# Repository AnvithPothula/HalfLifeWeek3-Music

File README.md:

# HalfLifeWeek3-Music
Guide: https://github.com/KaiPereira/MIDI-Keypad/blob/master/README.md

I followed the guide to create the MIDI keypad. However, I made some changes. I added a second encoder, and since I decided to use both encoders clicking functionalities, I had to remove the low-profile switches and a slider to make room on the ESP32. The remaining slider is used for volume, the first encoder for changing octaves, and the second encoder for adding a modulation effect. This is the final result of how the PCB looks like:

**3D Model / Final PCB Render:**

**Schematic:**

**Board Layout & Routing:**

Combined Layout:

Front Copper Layer:

Back Copper Layer:

**What it is and how it works:**

This project is a MIDI keyboard built around the Waveshare ESP32-S3-Zero microcontroller. All of the components fit together on a single two-layer PCB:

* **Waveshare ESP32-S3-Zero:** Kind of like the brain of the board. It reads all touch, switch, encoder, and analog inputs and sends USB MIDI messages to a computer or DAW.
* **Capacitive Touch Keys:** There are 7 copper pads in the front layer of the PCB. The ESP32-S3's built-in capacitive touch pins detect when your finger touches a pad to trigger MIDI note-on and note-off events.
* **2 EC11 Rotary Encoders:** One encoder adds a modulation effect, while the second encoder shifts the keypad's active octave up and down.
* **Slide Potentiometer:** Connected to the ESP32-S3's ADC pins and changes the volume.
* **3 SK6812 MINI-E NeoPixels:** RGB LEDs on the back that shine through holes in the PCB. They light up in different colors to indicate button presses and also show the current octave.

**Why I made it:**

I made this project to get more experience with KiCad PCB design (specifically working with custom footprints like capacitive touch pads and reverse-mount LEDs). Just like in Week 1, I wanted to push past the basic guide by adding both hardware and software upgrades.

**How to assemble and flash the firmware:**

**1. How to flash the firmware**
You can flash this board using the Arduino IDE (or CircuitPython/KMK):

1. Install the Arduino IDE.
2. In the Boards Manager, install the ESP32 boards package by Espressif and select Waveshare ESP32-S3-Zero (or ESP32S3 Dev Module) as your board.
3. Under the Tools menu, set USB Mode to USB-OTG (TinyUSB) and USB CDC On Boot to Enabled so the board is recognized as a native USB MIDI device.
4. Install these libraries in the Library Manager:
   * Adafruit TinyUSB Library (or Control Surface / MIDI library)
   * Adafruit NeoPixel
   * ESP32Encoder
5. Open midi-keyboard-arduino/midi-keyboard-arduino.ino, plug the board into your computer via USB-C, and click Upload. If it doesn't upload automatically, hold the BOOT button on the ESP32-S3-Zero, tap RESET, and release BOOT to enter bootloader mode.

**2. How to assemble the board**
To assemble the keypad, you need a soldering iron, solder, flux, tweezers, and flush cutters. Solder the components from shortest/surface-mount to tallest/through-hole:

1. **SK6812 MINI-E NeoPixels:** These are on the back of the PCB so they shine through the front holes. Align the angled/notched corner of each LED with the ground/orientation mark on the silkscreen, put one pad down, check that it sits flat over the hole, and solder the remaining three pads.
2. **Waveshare ESP32-S3-Zero:** Place it on its footprint with the USB-C port facing outward toward the top edge of the board. Solder one corner pin first to check alignment, then solder the rest of the pins and check for solder bridges.
3. **EC11 Rotary Encoders:** Push the mounting legs and signal pins through the front of the PCB. Bend the two large side mounting tabs slightly if needed to hold them flush, then solder the 3 signal pins, 2 switch pins, and mounting tabs on the back.
4. **Slide Potentiometer:** Insert the slide potentiometer on the front of the board, make sure it sits completely straight and flat, and solder all pins on the back.
5. **Knobs:** Push the knobs onto the rotary encoders and slide potentiometers.

Before plugging in the USB-C cable, use a multimeter in continuity mode to make sure 3V3/5V and GND are not shorted. Once verified, plug it in, flash the firmware, and test the capacitive keys and encoders!

**BOM:**

| Item | Qty | Supplier | Cost/item | Total cost | Link |
| --- | ---: | --- | ---: | ---: | --- |
| ESP32-S3-Zero | 1 | AliExpress | $4.32 | $4.32 | [AliExpress](https://www.aliexpress.us/item/3256807949476561.html) |
| EC11 Rotary Encoder 20mm (5-pack) | 1 | AliExpress | $3.36 | $3.36 | [AliExpress](https://www.aliexpress.us/item/3256808530463909.html) |
| SK6812 MINI-E NeoPixels (20-pack) | 1 | AliExpress | $2.54 | $2.54 | [AliExpress](https://www.aliexpress.us/item/3256805007401420.html) |
| 45mm Slide Potentiometer B10K (5-pack) | 1 | AliExpress | $5.13 | $5.13 | [AliExpress](https://www.aliexpress.us/item/3256808872395865.html) |
| PCB | 1 | JLCPCB | $4.00 | $4.00 | [JLCPCB](https://jlcpcb.com/) |
| Shipping (AliExpress Choice) | — | AliExpress | — | $0.00 | — |
| Shipping (JLCPCB Global Standard Direct Line) | — | JLCPCB | — | $8.37 | — |
| Estimated sales tax (8.125% on AliExpress parts) | — | — | — | $1.25 | — |
| **Estimated total** |  |  |  | **$28.97** |  |

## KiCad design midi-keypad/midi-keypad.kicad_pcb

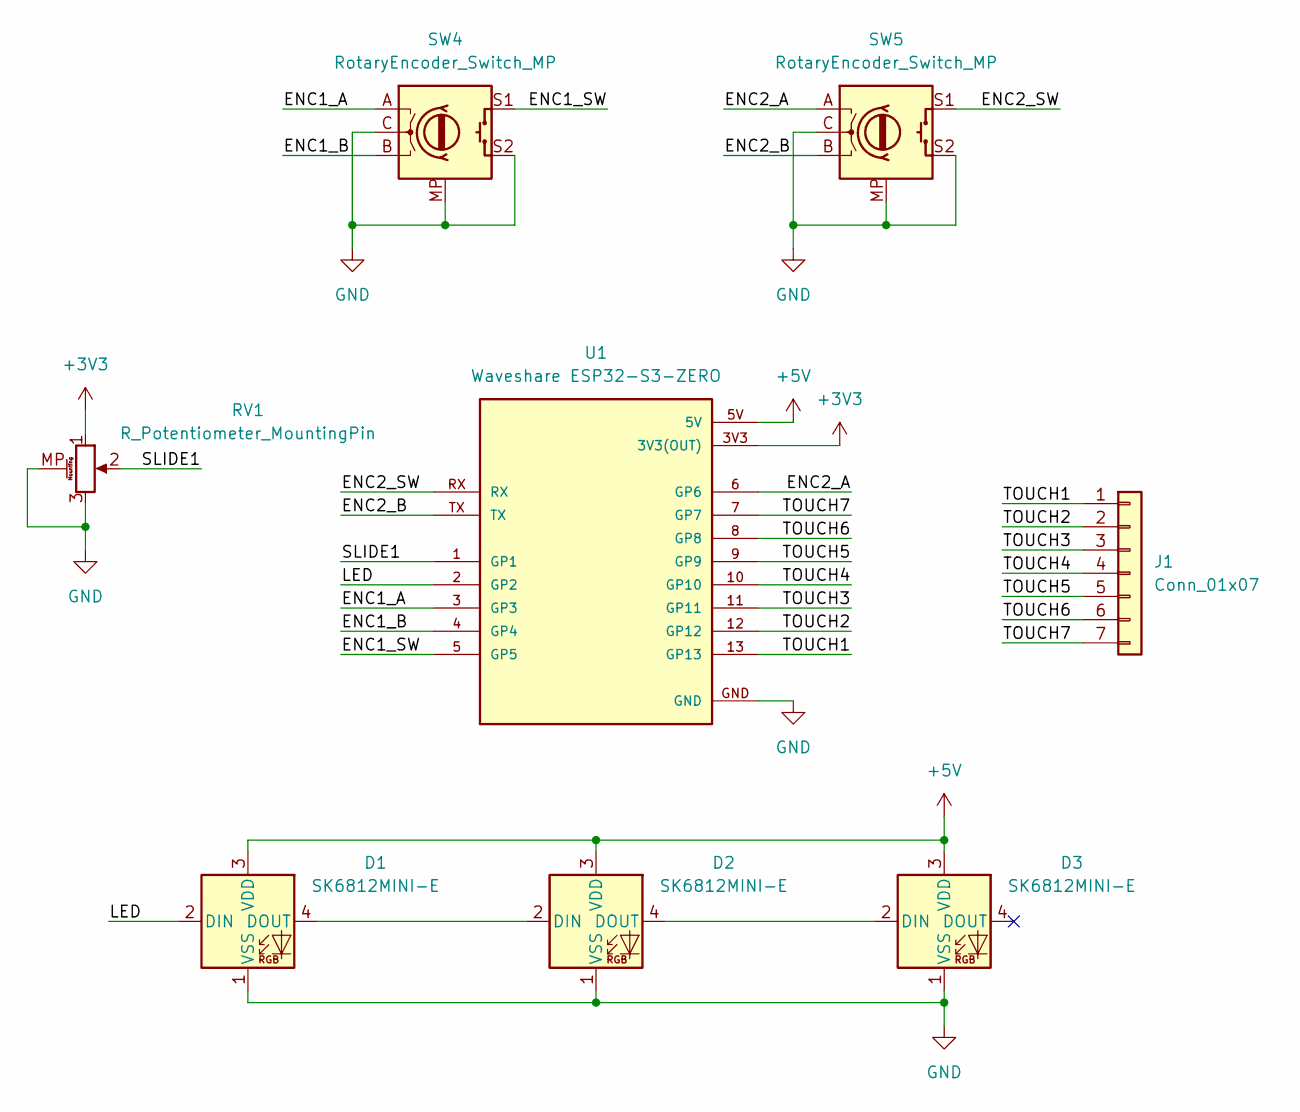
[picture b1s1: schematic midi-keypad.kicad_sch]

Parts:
D1, D2, D3: SK6812MINI-E; LED_SK6812MINI-E_3.2x2.8mm_P1.5mm_ReverseMount
J1: Conn_01x07; Capacitive Keys_7
RV1: R_Potentiometer_MountingPin; Potentiometer_Bourns_PTA1543_Single_Slide
SW4, SW5: RotaryEncoder_Switch_MP; RotaryEncoder_Alps_EC11E-Switch_Vertical_H20mm
U1: Waveshare ESP32-S3-ZERO; Waveshare ESP32-S3-Zero; PARTREV NA

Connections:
+3V3: RV1.1, U1.3V3 (3V3(OUT))
+5V: D1.3 (VDD), D2.3 (VDD), D3.3 (VDD), U1.5V
/ENC1_A: SW4.A, U1.3 (GP3)
/ENC1_B: SW4.B, U1.4 (GP4)
/ENC1_SW: SW4.S1, U1.5 (GP5)
/ENC2_A: SW5.A, U1.6 (GP6)
/ENC2_B: SW5.B, U1.TX
/ENC2_SW: SW5.S1, U1.RX
/LED: D1.2 (DIN), U1.2 (GP2)
/SLIDE1: RV1.2, U1.1 (GP1)
/TOUCH1: J1.1, U1.13 (GP13)
/TOUCH2: J1.2, U1.12 (GP12)
/TOUCH3: J1.3, U1.11 (GP11)
/TOUCH4: J1.4, U1.10 (GP10)
/TOUCH5: J1.5, U1.9 (GP9)
/TOUCH6: J1.6, U1.8 (GP8)
/TOUCH7: J1.7, U1.7 (GP7)
GND: D1.1 (VSS), D2.1 (VSS), D3.1 (VSS), RV1.3, RV1.MP (MountPin), SW4.C, SW4.MP, SW4.S2, SW5.C, SW5.MP, SW5.S2, U1.GND
unnamed: D1.4 (DOUT), D2.2 (DIN)
unnamed: D2.4 (DOUT), D3.2 (DIN)

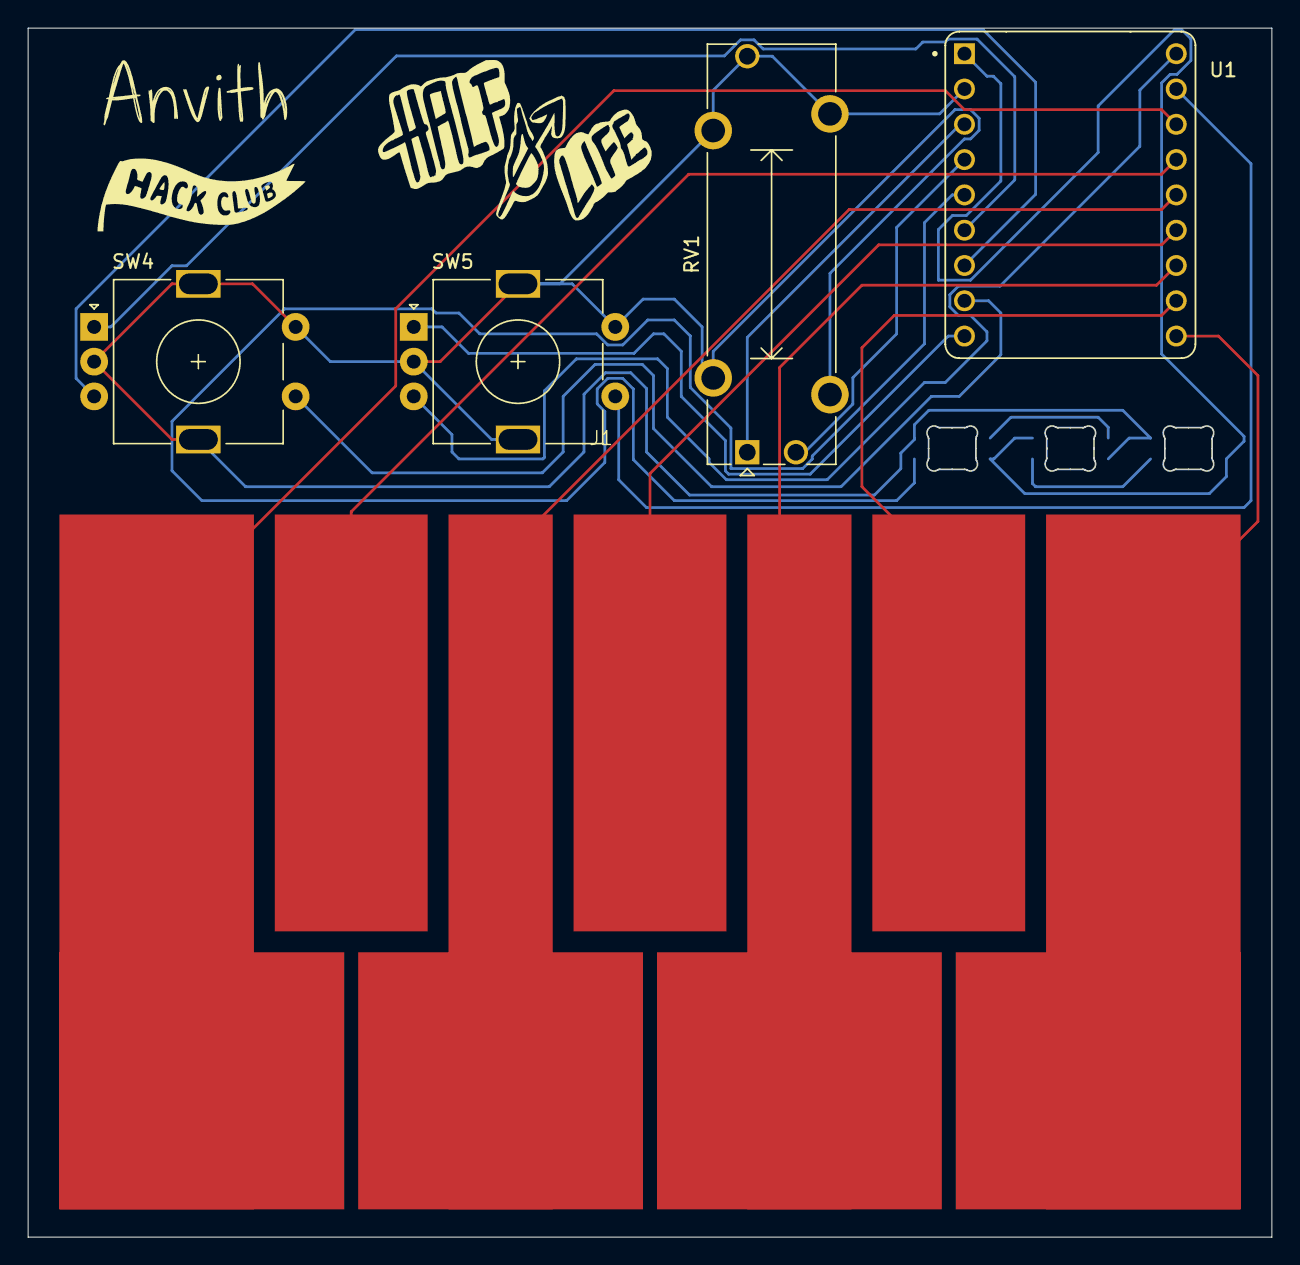
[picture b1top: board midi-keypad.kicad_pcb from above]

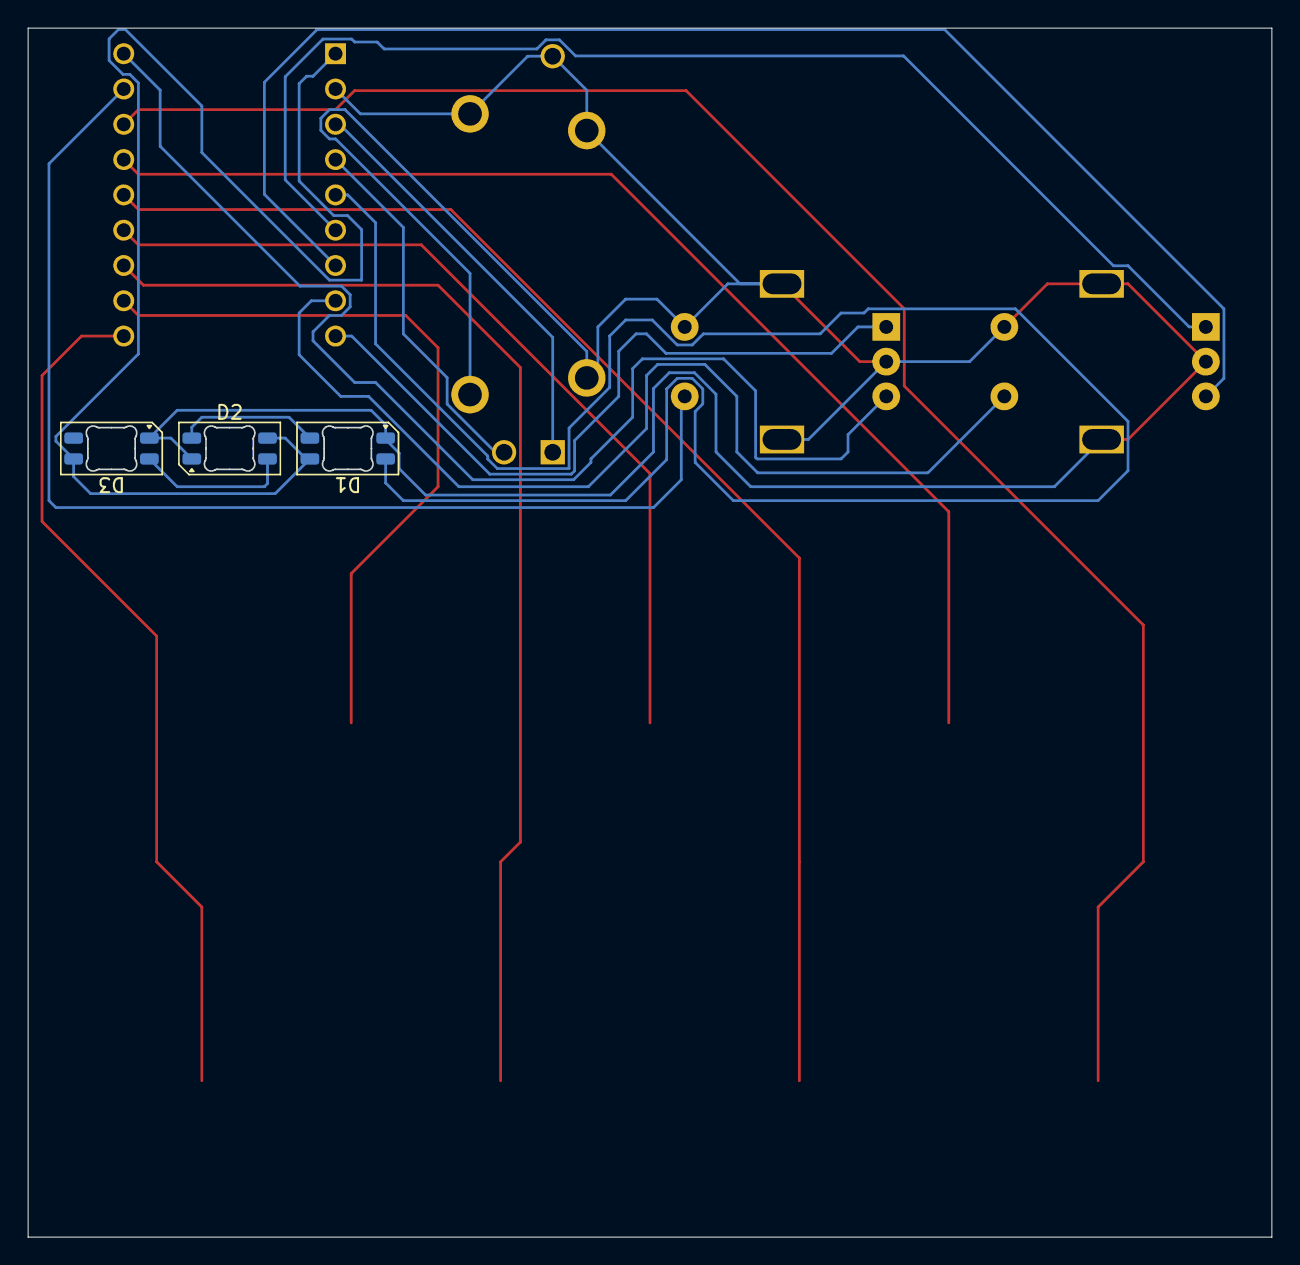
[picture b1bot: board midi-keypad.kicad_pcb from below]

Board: 2 copper layers, 89.5 x 87.0 mm, 8 parts (3 on the bottom side), 20 nets.

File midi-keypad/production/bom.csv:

Designator,Footprint,Quantity,Value,LCSC Part #
"D1, D2, D3",LED_SK6812MINI-E_3.2x2.8mm_P1.5mm_ReverseMount,3,SK6812MINI-E,
J1,Capacitive Keys_7,1,Conn_01x07,
RV1,Potentiometer_Bourns_PTA1543_Single_Slide,1,R_Potentiometer_MountingPin,
"SW4, SW5",RotaryEncoder_Alps_EC11E-Switch_Vertical_H20mm,2,RotaryEncoder_Switch_MP,
U1,Waveshare ESP32-S3-Zero,1,Waveshare ESP32-S3-ZERO,

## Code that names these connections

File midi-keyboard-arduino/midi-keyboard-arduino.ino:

#include <Arduino.h>
#include "USB.h"
#include "USBMIDI.h"
#include <Adafruit_NeoPixel.h>

USBMIDI MIDI;

const int SLIDER_PIN = 1;
const int LED_PIN    = 2;
const int NUM_LEDS   = 3;

const int ENC1_A_PIN  = 3;
const int ENC1_B_PIN  = 4;
const int ENC1_SW_PIN = 5;

const int ENC2_A_PIN  = 6;
const int ENC2_B_PIN  = 43; // TX
const int ENC2_SW_PIN = 44; // RX

const int TOUCH_PINS[7] = {13, 12, 11, 10, 9, 8, 7}; // TOUCH1-7, GP13-7
const uint8_t TOUCH_BASE_NOTES[7] = {60, 62, 64, 65, 67, 69, 71}; // C4-B4

Adafruit_NeoPixel pixels(NUM_LEDS, LED_PIN, NEO_GRB + NEO_KHZ800); // neopixels

uint32_t touchBaselines[7] = {0};
int touchPlaying[7] = {-1, -1, -1, -1, -1, -1, -1}; // -1 = not playing

int octaveOffset = 0; // clamped b/w -4 and +4
int modCCValue   = 0; // clamped b/w 0 and 127
int lastSliderVal = -1;

int lastEnc1A = HIGH;
bool enc1SwWasPressed = false;
unsigned long lastEnc1SwTime = 0;

int lastEnc2A = HIGH;
bool enc2SwWasPressed = false;
unsigned long lastEnc2SwTime = 0;

// update neopixel colors
void updateLEDs() {
  bool anyKeyPressed = false;
  for (int i = 0; i < 7; i++) {
    if (touchPlaying[i] != -1) {
      anyKeyPressed = true;
      break;
    }
  }

  uint32_t color = 0;
  if (anyKeyPressed) {
    color = pixels.Color(255, 255, 255); // flash white when a key pressed
  } else {
    switch (octaveOffset) {
      case -4: color = pixels.Color(0, 0, 128);   break; // deep blue
      case -3: color = pixels.Color(0, 0, 255);   break; // blue
      case -2: color = pixels.Color(0, 128, 255); break; // sky blue
      case -1: color = pixels.Color(0, 255, 255); break; // cyan
      case  0: color = pixels.Color(0, 255, 0);   break; // green (I made this the default)
      case  1: color = pixels.Color(180, 255, 0); break; // lime
      case  2: color = pixels.Color(255, 255, 0); break; // yellow
      case  3: color = pixels.Color(255, 100, 0); break; // orange
      case  4: color = pixels.Color(255, 0, 0);   break; // red
      default: color = pixels.Color(0, 255, 0);   break;
    }
  }

  for (int i = 0; i < NUM_LEDS; i++) {
    pixels.setPixelColor(i, color);
  }
  pixels.show();
}

void setup() {
  // encoder 1
  pinMode(ENC1_A_PIN, INPUT_PULLUP);
  pinMode(ENC1_B_PIN, INPUT_PULLUP);
  pinMode(ENC1_SW_PIN, INPUT_PULLUP);
  lastEnc1A = digitalRead(ENC1_A_PIN);

  // encoder 2
  pinMode(ENC2_A_PIN, INPUT_PULLUP);
  pinMode(ENC2_B_PIN, INPUT_PULLUP);
  pinMode(ENC2_SW_PIN, INPUT_PULLUP);
  lastEnc2A = digitalRead(ENC2_A_PIN);

  // slider res (12-bit: 0-4095)
  analogReadResolution(12);

  // neopixels
  pixels.begin();
  pixels.setBrightness(75); // 0-255

  // calibrate capacitive touch pads
  delay(300);
  for (int i = 0; i < 7; i++) {
    uint64_t sum = 0;
    for (int sample = 0; sample < 16; sample++) {
      sum += touchRead(TOUCH_PINS[i]);
      delay(5);
    }
    touchBaselines[i] = sum / 16;
  }

  MIDI.begin();
  USB.begin();

  updateLEDs();
}

void loop() {
  unsigned long now = millis();

  // read encoder 1 (the octave shift one)
  int currentEnc1A = digitalRead(ENC1_A_PIN);
  if (currentEnc1A != lastEnc1A && currentEnc1A == LOW) {
    if (digitalRead(ENC1_B_PIN) != currentEnc1A) {
      octaveOffset = min(4, octaveOffset + 1);
    } else {
      octaveOffset = max(-4, octaveOffset - 1);
    }
    updateLEDs();
  }
  lastEnc1A = currentEnc1A;

  // clicking encoder 1 (resets octave to 0)
  bool enc1Pressed = (digitalRead(ENC1_SW_PIN) == LOW);
  if (enc1Pressed && !enc1SwWasPressed && (now - lastEnc1SwTime > 50)) {
    octaveOffset = 0;
    updateLEDs();
    enc1SwWasPressed = true;
    lastEnc1SwTime = now;
  } else if (!enc1Pressed && (now - lastEnc1SwTime > 50)) {
    enc1SwWasPressed = false;
  }

  // read encoder 2 (the mod wheel one)
  int currentEnc2A = digitalRead(ENC2_A_PIN);
  if (currentEnc2A != lastEnc2A && currentEnc2A == LOW) {
    if (digitalRead(ENC2_B_PIN) != currentEnc2A) {
      modCCValue = min(127, modCCValue + 4);
    } else {
      modCCValue = max(0, modCCValue - 4);
    }
    MIDI.controlChange(1, modCCValue, 1);
  }
  lastEnc2A = currentEnc2A;

  // clicking encoder 2 (resets modulation to 0)
  bool enc2Pressed = (digitalRead(ENC2_SW_PIN) == LOW);
  if (enc2Pressed && !enc2SwWasPressed && (now - lastEnc2SwTime > 50)) {
    modCCValue = 0;
    MIDI.controlChange(1, modCCValue, 1);
    enc2SwWasPressed = true;
    lastEnc2SwTime = now;
  } else if (!enc2Pressed && (now - lastEnc2SwTime > 50)) {
    enc2SwWasPressed = false;
  }

  // scan keys
  for (int i = 0; i < 7; i++) {
    uint32_t reading = touchRead(TOUCH_PINS[i]);
    bool isTouched = (reading > (touchBaselines[i] + (touchBaselines[i] / 4)));

    if (isTouched && touchPlaying[i] == -1) {
      int note = TOUCH_BASE_NOTES[i] + (octaveOffset * 12);
      note = max(0, min(127, note));
      MIDI.noteOn(note, 127, 1);
      touchPlaying[i] = note;
      updateLEDs();
    } else if (!isTouched && touchPlaying[i] != -1) {
      MIDI.noteOff(touchPlaying[i], 0, 1);
      touchPlaying[i] = -1;
      updateLEDs();
    }
  }

  // reads volume slider
  int rawSlider = analogRead(SLIDER_PIN); // 0-4095
  int sliderCC = rawSlider >> 5;
  if (abs(sliderCC - lastSliderVal) > 1) {
    MIDI.controlChange(7, sliderCC, 1);
    lastSliderVal = sliderCC;
  }

  delay(2);
}
